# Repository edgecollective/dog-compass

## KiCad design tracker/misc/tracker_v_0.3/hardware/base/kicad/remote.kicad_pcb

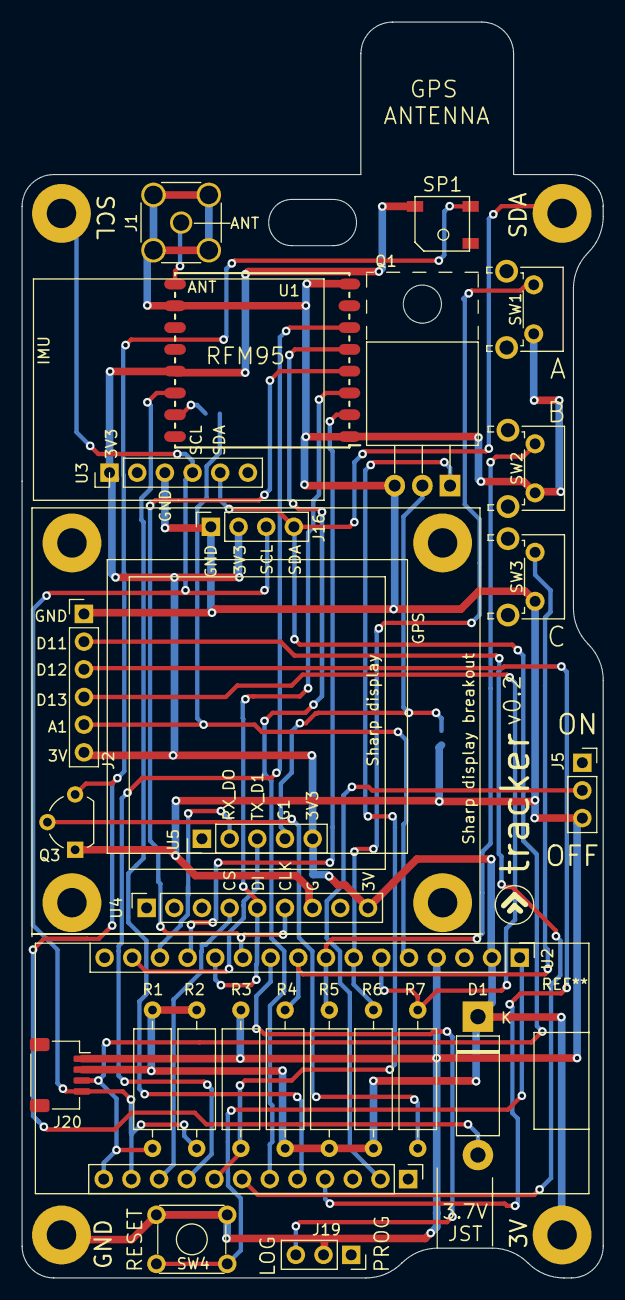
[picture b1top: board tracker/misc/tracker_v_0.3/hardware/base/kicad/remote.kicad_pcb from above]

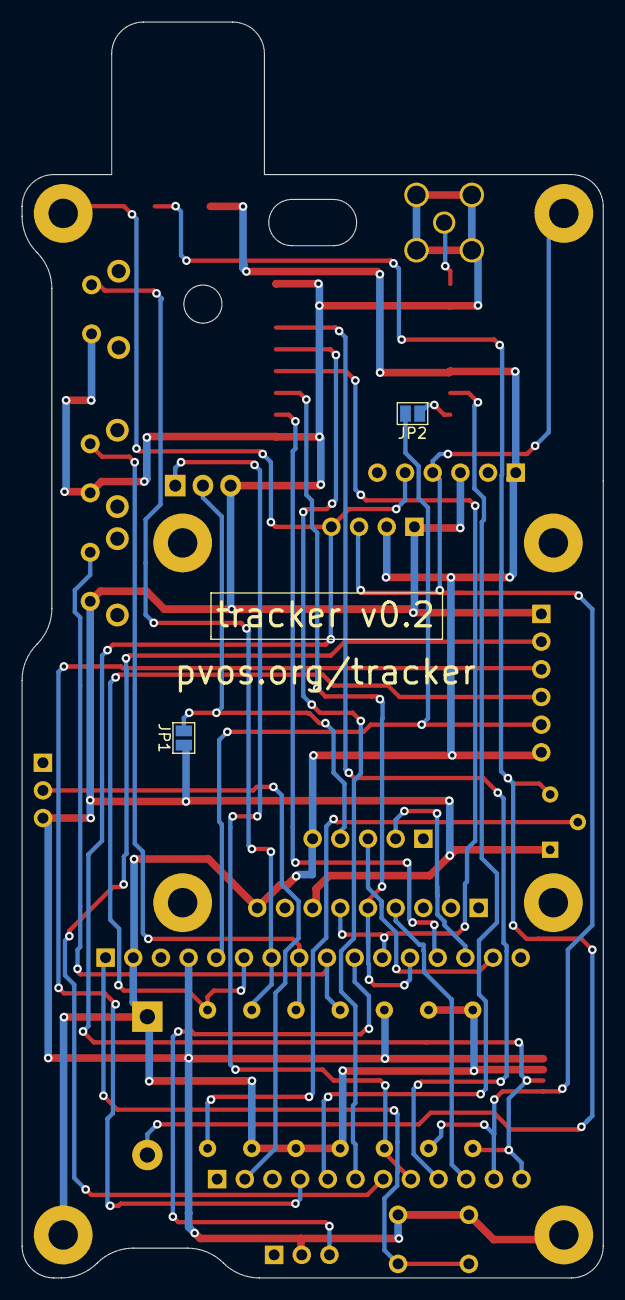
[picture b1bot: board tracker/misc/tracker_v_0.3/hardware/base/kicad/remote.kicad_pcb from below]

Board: 2 copper layers, 53.3 x 115.3 mm, 32 parts (2 on the bottom side), 29 nets.

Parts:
D1: DIODE; D_5W_P12.70mm_Horizontal
H1, H2, H5, H6: MountingHole_Pad; MountingHole_2.7mm_M2.5_Pad
J1: Conn_Coaxial; SMA_Amphenol_132134_Vertical
J2: Conn_01x06_Female; PinHeader_1x06_P2.54mm_Vertical
J5, J19: Conn_01x03_Female; PinSocket_1x03_P2.54mm_Vertical
J16: Conn_01x04_Female; PinSocket_1x04_P2.54mm_Vertical
J20: Conn_01x04_Female; JST_SH_SM04B-SRSS-TB_1x04-1MP_P1.00mm_Horizontal
JP1, JP2: Jumper_NO_Small; SolderJumper-2_P1.3mm_Open_Pad1.0x1.5mm
Q1: Q_NMOS_GDS; TO-220-3_Horizontal_TabUp
Q3: Q_NPN_EBC; TO-92L_Wide
R1, R2, R4, R5, R6: 4.7K; R_Axial_DIN0309_L9.0mm_D3.2mm_P12.70mm_Horizontal
R3: 10K; R_Axial_DIN0309_L9.0mm_D3.2mm_P12.70mm_Horizontal
R7: R; R_Axial_DIN0309_L9.0mm_D3.2mm_P12.70mm_Horizontal
SP1: SPEAKER_BUZZER5MM; BUZZER_SMT_5MM
SW1, SW2, SW3: SW_Push; SW_Tactile_SPST_Angled_PTS645Vx58-2LFS
SW4: SW_Push_Dual; SW_TH_Tactile_Omron_B3F-10xx
U1: RFM95HW; RFM95
U2: feather
U3: Adafruit_IMU_BNO005; IMU_Ada_BNO005
U4: Adafruit_Sharp_Display_1_3; Display_adafruit_sharp_13
U5: neo-6m-black; gps_neo6m_black

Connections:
+3V3: D1.1, H2.1, J2.6, J16.2, J20.2, R1.1, R2.1, R4.1, R5.1, R6.1, SP1.-, U1.13, U2.14, U3.1, U4.9, U5.5
A0: J2.5, JP2.2, U2.17
A1: J2.4, R7.2, U2.18
A2: R6.2, SW1.1, U2.19
A3: R5.2, SW2.1, U2.20
A4: R4.2, SW3.1, U2.21
A5: J19.3, U2.22
D5: U2.10, U4.4
D6: U1.6, U2.9
D9: Q1.1, R3.1, U2.8
D10: J2.2, U2.7
D11: U1.5, U2.6
D12: U1.14, U2.5
D13: J2.3, U2.4
EN: J5.2, U2.2
GND: H1.1, J1.2, J2.1, J5.3, J16.1, J19.2, J20.1, JP1.1, Q1.3, Q3.1, R3.2, SW1.2, SW2.2, SW3.2, SW4.3, SW4.4, U1.1, U1.8, U1.10, U2.16, U3.3, U4.7
MISO: U1.2, U2.25
MOSI: U1.3, U2.24, U4.5
unnamed: D1.2, Q3.3, SP1.+
unnamed: J1.1, U1.9
unnamed: JP2.1, U1.15
unnamed: Q3.2, R7.1
POWER_1: JP1.2, Q1.2, U5.4
RX_D0: U2.26, U5.2
SCK: U1.4, U2.23, U4.6
SCL: H6.1, J16.3, J20.4, R2.2, U2.11, U3.4
SDA: H5.1, J16.4, J20.3, R1.2, U2.12, U3.5
TX_D1: U2.27, U5.3
~RESET: SW4.1, SW4.2, U2.13

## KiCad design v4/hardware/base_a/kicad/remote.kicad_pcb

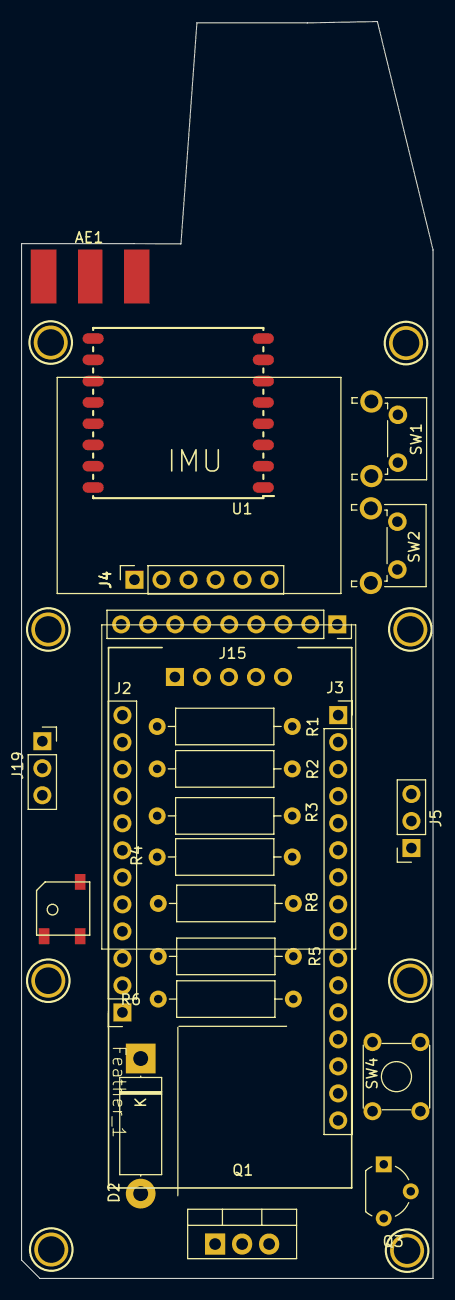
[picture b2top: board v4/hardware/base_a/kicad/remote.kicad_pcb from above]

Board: 2 copper layers, 38.7 x 118.2 mm, 31 parts (1 on the bottom side), 20 nets, no tracks yet.

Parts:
AE1: Antenna_Shield; RF_SMA_BoardEdge_142-0701-801
D2: DIODE; D_5W_P12.70mm_Horizontal
H3, H4, H7, H8, H9, H10, H11, H12: MountingHole; MOUNTINGHOLE_2.5_PLATED
J2: Conn_01x12_Female; PinSocket_1x12_P2.54mm_Vertical
J3: Conn_01x16_Female; PinSocket_1x16_P2.54mm_Vertical
J4: Conn_01x06_Female; PinSocket_1x06_P2.54mm_Vertical
J5, J19: Conn_01x03_Female; PinSocket_1x03_P2.54mm_Vertical
J6: Conn_01x05_Female; PinSocket_1x05_P2.54mm_Vertical
J15: Conn_01x09_Female; PinSocket_1x09_P2.54mm_Vertical
Q1: Q_NMOS_GDS; TO-220-3_Vertical
Q3: Q_NPN_EBC; TO-92L_Wide
R1, R2, R3, R4: 4.7K; R_Axial_DIN0309_L9.0mm_D3.2mm_P12.70mm_Horizontal
R5, R8: R; R_Axial_DIN0309_L9.0mm_D3.2mm_P12.70mm_Horizontal
R6: 10K; R_Axial_DIN0309_L9.0mm_D3.2mm_P12.70mm_Horizontal
SP1: SPEAKER_BUZZER5MM; BUZZER_SMT_5MM
SW1, SW2: SW_Push; SW_Tactile_SPST_Angled_PTS645Vx58-2LFS
SW4: SW_Push_Dual; SW_TH_Tactile_Omron_B3F-10xx
U1: RFM95HW; RFM95

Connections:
+3V3: D2.1 (K), J3.15, J4.1, J6.5, J15.1, R1.1, R2.1, R3.1, R4.1, SP1.-
A0: J3.12, R8.2
A3: J3.9, J19.3
A4: J3.8, R4.2, SW1.1
A5: J3.7, R3.2, SW2.1
D5: J2.10, J15.6
D9: J2.8, Q1.1 (G), R6.1
GND: J3.13, J4.3, J5.1, J15.3, Q1.3 (S), Q3.1 (E), R5.2, R6.2, SW1.2, SW2.2, SW4.3, SW4.4
MOSI: J3.5, J15.5
unnamed: D2.2 (A), Q3.3 (C), SP1.+
unnamed: J19.2, R5.1
unnamed: Q3.2 (B), R8.1
POWER_1: J6.4, Q1.2 (D)
RX_D0: J3.3, J6.2
SCK: J3.6, J15.4
SCL: J2.11, J4.4, R2.2
SDA: J2.12, J4.5, R1.2
TX_D1: J3.2, J6.3
VBAT: J2.1, J5.2
~RESET: J3.16, SW4.1, SW4.2

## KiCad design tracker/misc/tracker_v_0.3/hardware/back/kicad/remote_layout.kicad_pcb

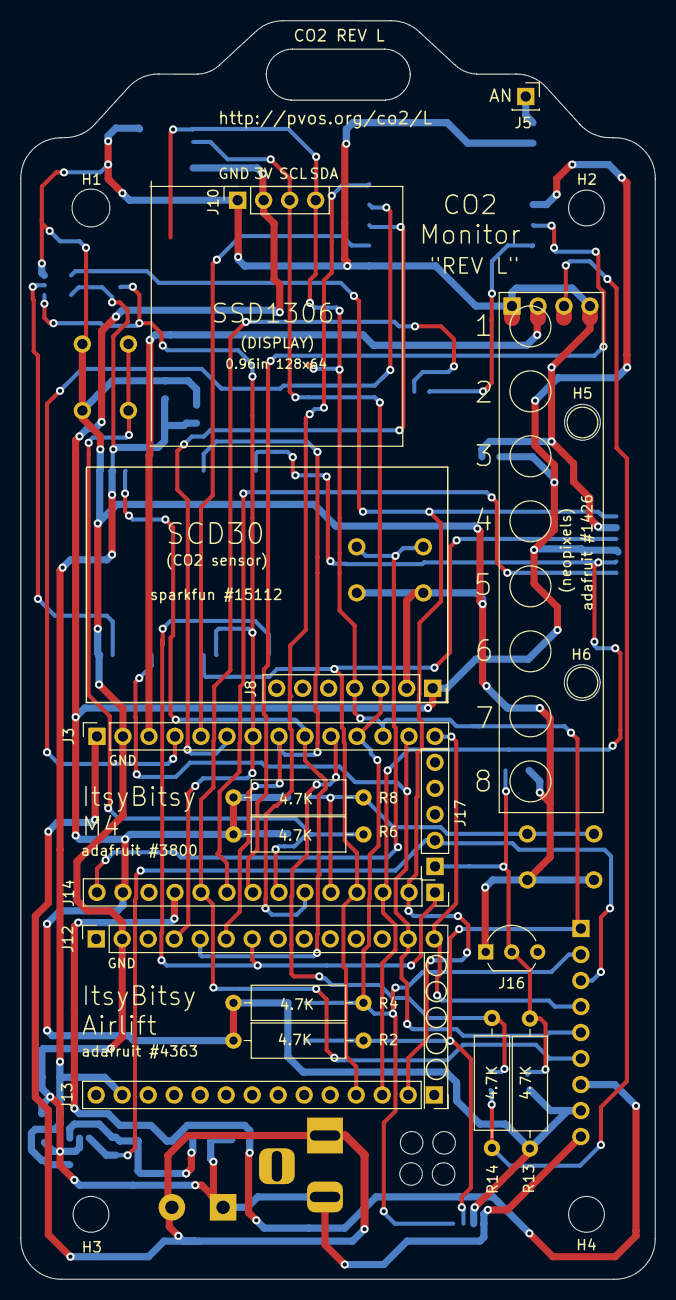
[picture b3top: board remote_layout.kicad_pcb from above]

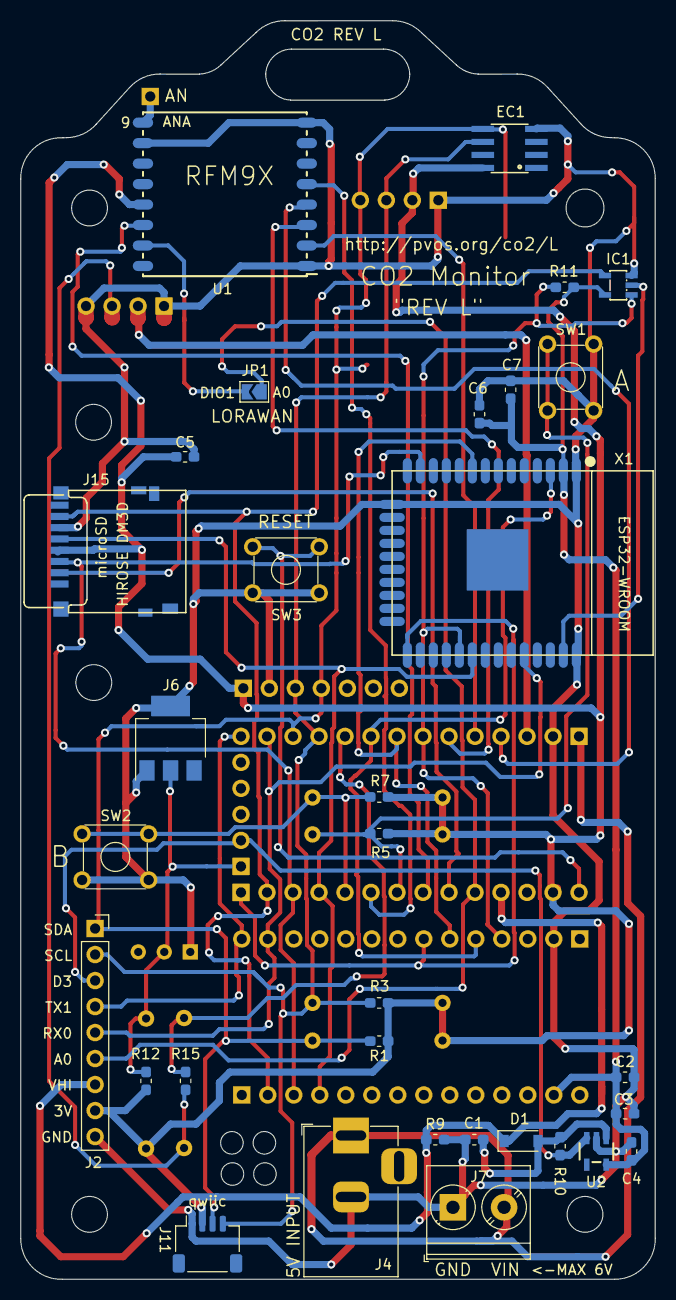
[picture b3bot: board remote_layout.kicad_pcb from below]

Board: 2 copper layers, 62.0 x 122.9 mm, 62 parts (32 on the bottom side), 35 nets.

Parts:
C1, C3, C4, C7: 10u; C_0603_1608Metric_Pad1.05x0.95mm_HandSolder
C2, C6: 0.1u; C_0603_1608Metric_Pad1.05x0.95mm_HandSolder
C5: 1u; C_0603_1608Metric_Pad1.05x0.95mm_HandSolder
D1: DIODE; D_SOD-123
EC1: ATECC108; SOIC8
H1: MountingHole; MountingHole_3.7mm
H2, H3, H4, H5, H6: MountingHole; MountingHole_3.5mm
H7, H8, H9, H10: MountingHole; MountingHole_2.2mm_M2
IC1: 74AHC1G125; SOT23-5L
J1: Conn_01x04_Female; PinSocket_1x04_P2.54mm_Vertical_no_silk
J2: Conn_01x09_Female; PinSocket_1x09_P2.54mm_Vertical
J3, J12, J13, J14: Conn_01x14_Female; PinSocket_1x14_P2.54mm_Vertical
J4: Barrel_Jack_MountingPin; BarrelJack_Horizontal
J5: Conn_01x01_Female; PinSocket_1x01_P2.54mm_Vertical
J6: Conn_01x04_Female; SOT-223
J7: Screw_Terminal_01x02; TerminalBlock_Phoenix_PT-1,5-2-5.0-H_1x02_P5.00mm_Horizontal
J8: SCD30; PinSocket_1x07_P2.54mm_Vertical
J10: ssd1306; PinSocket_1x04_P2.54mm_Vertical
J11: Conn_01x04_Female; JST_SH_SM04B-SRSS-TB_1x04-1MP_P1.00mm_Horizontal
J15: Micro_SD_Card; DM3D-SF_outline
J16: Conn_01x03_Female; TO-92_Inline_Wide
J17: Conn_01x05_Female; PinSocket_1x05_P2.54mm_Vertical
JP1: Jumper_NO_Small; SolderJumper-2_P1.3mm_Open_TrianglePad1.0x1.5mm
R1, R3: R; R_0603_1608Metric_Pad1.05x0.95mm_HandSolder
R2, R4: R; R_Axial_DIN0309_L9.0mm_D3.2mm_P12.70mm_Horizontal
R5, R7, R12: 4.7K; R_0603_1608Metric_Pad1.05x0.95mm_HandSolder
R6, R8, R13: 4.7K; R_Axial_DIN0309_L9.0mm_D3.2mm_P12.70mm_Horizontal
R9, R10: 100k; R_0603_1608Metric_Pad1.05x0.95mm_HandSolder
R11: 10K; R_0603_1608Metric_Pad1.05x0.95mm_HandSolder
R14: 500; R_Axial_DIN0309_L9.0mm_D3.2mm_P12.70mm_Horizontal
R15: 500; R_0603_1608Metric_Pad1.05x0.95mm_HandSolder
SW1, SW2, SW3: SW_Push_Dual; SW_TH_Tactile_Omron_B3F-10xx
TP1, TP2, TP3, TP4: TestPoint; TestPoint_Pad_1.0x1.0mm_no_silk
U1: RFM95HW; RFM95
U2: VREG_SOT23-5; SOT23-5
X1: ESP32_WROOM32; ESP32-WROOM

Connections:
2_ESP_GPIO0: J12.7, J14.1, X1.25
3VESP: C2.1, C3.1, C4.1, C6.1, C7.1, IC1.5, J13.13, R11.1, U2.5, X1.2
3_LDO_ENABLE: J2.3, J17.2, R10.2, U2.3
4_SERDAT: J6.2, J16.2, J17.1, R12.2, R13.2
5_NEOPIXEL: J3.10, R14.2, R15.2
7_ESP_RESET: J3.9, J12.5, X1.3
9_ESP_BUSY: J3.8, J12.6, X1.9
10_ESP_CS: IC1.1, J3.7, J12.4, R11.2, X1.29
11_LORA_MOSI: J3.6, U1.3
12_LORA_MISO: J3.5, U1.2
13_LORA_SCK: J3.4, U1.4
+3V3: C5.1, EC1.8, J2.8, J8.1, J10.2, J11.2, J14.13, J15.4, R1.1, R2.1, R3.1, R4.1, R5.1, R6.1, R7.1, R8.1, R12.1, R13.1, U1.13
A0_LORAWAN: J2.6, J14.10, JP1.1
A1_SD_CS: J14.9, J15.2
A2_LORA_IRQ: J14.8, U1.14
A3_BUTTON_A: J14.7, R5.2, R6.2, SW1.1, SW1.2
A4_LORA_CS: J14.6, U1.5
A5_BUTTON_B: J14.5, R7.2, R8.2, SW2.1, SW2.2
ESP_MISO: IC1.2, X1.37
ESP_RX: J2.5, J3.13, J12.13, X1.34
EXP_TX: J2.4, J3.14, J12.14
GND: C1.2, C2.2, C3.2, C4.2, C5.2, C6.2, C7.2, EC1.4, IC1.3, J1.1, J1.4, J2.9, J3.2, J4.2, J6.1, J6.4, J7.1, J8.2, J10.1, J11.1, J12.2, J15.6, J16.1, R9.2, SW1.3, SW1.4, SW2.3, SW2.4, SW3.3, SW3.4, TP1.1, TP4.1, U1.1, U1.8, U1.10, U2.2, X1.1, X1.15, X1.38
LORA_DIO1: JP1.2, U1.15
MISO: IC1.4, J13.2, J14.2, J15.7
MOSI: J13.3, J14.3, J15.3, X1.13
unnamed: C1.1, D1.2, R10.1, U2.1
unnamed: J1.3, R14.1, R15.1, TP3.1
unnamed: J5.1, U1.9
SCK: J13.4, J14.4, J15.5, X1.30
SCL: EC1.6, J2.2, J3.11, J8.3, J10.3, J11.4, R3.2, R4.2
SDA: EC1.5, J2.1, J3.12, J8.4, J10.4, J11.3, R1.2, R2.2
VBAT: J3.1, J4.1, J7.2
VBUS: J1.2, J3.3, TP2.1
VHI: D1.1, J2.7, J14.11, R9.1
~RESET: J14.14, SW3.1, SW3.2

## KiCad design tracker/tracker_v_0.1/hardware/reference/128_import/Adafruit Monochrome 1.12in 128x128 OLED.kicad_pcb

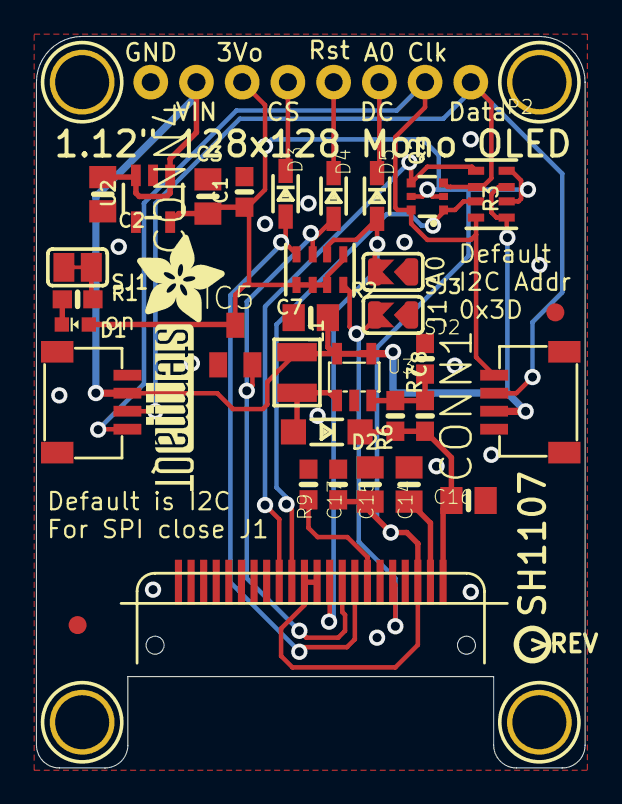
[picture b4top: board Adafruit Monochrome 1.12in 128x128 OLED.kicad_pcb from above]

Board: 2 copper layers, 30.5 x 40.6 mm, 41 parts (0 on the bottom side), 21 nets.

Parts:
C1, C8: 0.1uF; 0603-NO
C2, C3, C7, C14, C15, C16: 10uF; 0805-NO
C17: 1uF; 0603-NO
CONN1, CONN4: STEMMA_I2C_QT; JST_SH4
D1: GREEN; CHIPLED_0603_NOOUTLINE
D2: MBR120; SOD-123
D3, D4, D5: 1N4148; SOD-323
FID3, FID4: FIDUCIAL_1MM
IC5: APX803; SOT23
JP2: HEADER-1X876MIL; 1X08_ROUND_76
L1: 10uH; INDUCTOR_1007
Q2: BSS138; SOT363
R1, R7: 10K; 0603-NO
R2, R3: 10K; RESPACK_4X0603
R6: 100K; 0603-NO
R9: 390K; 0603-NO
SJ1: SOLDERJUMPERCLOSED; SOLDERJUMPER_CLOSEDWIRE
SJ2, SJ3: SOLDERJUMPER; SOLDERJUMPER_ARROW_NOPASTE
U2: AP2112K-3.3; SOT23-5
U3: FAN5331SX; SOT23-5@1
U$1, U$17, U$19, U$21: MOUNTINGHOLE3.0THIN; MOUNTINGHOLE_3.0_PLATEDTHIN
U$8: ADAFRUIT_5MM
U$25: PCBFEAT-REV-040
U$31: STEMMAQT
X2: OLED_1.12_128X128_MONO; OLED_1.12IN_128X128MONO

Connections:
3.3V: C1.1, C3.1, C15.2, C17.2, D1.A, IC5.3, JP2.6, Q2.2, Q2.5, R2.1, R2.5, R2.6, R2.7, R3.2, R3.4, U2.5, X2.3, X2.11, X2.12
12V: C8.1, C16.2, D2.C, R6.2, X2.1
/CS_3.3V: D3.A, R2.4, X2.8
/CS_5.0V: D3.C, JP2.5
/D0/SCLK/SCK_3.3V: Q2.1, R3.7, X2.13
/D1/MOSI/SDA1_3.3V: Q2.4, R3.5, X2.14
/DC/SA0_3.3V: D5.A, R2.2, SJ3.2, X2.10
/DC/SA0_5.0V: D5.C, JP2.3
/RST_3.3V: D4.A, IC5.2, R2.3, X2.9
/RST_5.0V: D4.C, JP2.4
/SCL: CONN1.4, CONN4.4, JP2.2, Q2.6, R3.8
/SDA: CONN1.3, CONN4.3, JP2.1, Q2.3, R3.6
GND: C1.2, C2.2, C3.2, C7.2, C14.1, C15.1, C16.1, C17.1, CONN1.1, CONN4.1, IC5.1, JP2.8, R7.1, R9.1, SJ1.2, SJ2.1, SJ3.1, U2.2, U3.2, X2.4, X2.6, X2.15, X2.16, X2.17, X2.18, X2.19, X2.20, X2.21, X2.22
unnamed: C8.2, R6.1, R7.2, U3.3
unnamed: C14.2, X2.2
unnamed: D1.C, R1.1
unnamed: D2.A, L1.P$2, U3.1
unnamed: R1.2, SJ1.1
unnamed: R2.8, SJ2.2, X2.5
unnamed: R9.2, X2.7
VCC: C2.1, C7.1, CONN1.2, CONN4.2, JP2.7, L1.P$1, R3.1, R3.3, U2.1, U2.3, U3.4, U3.5

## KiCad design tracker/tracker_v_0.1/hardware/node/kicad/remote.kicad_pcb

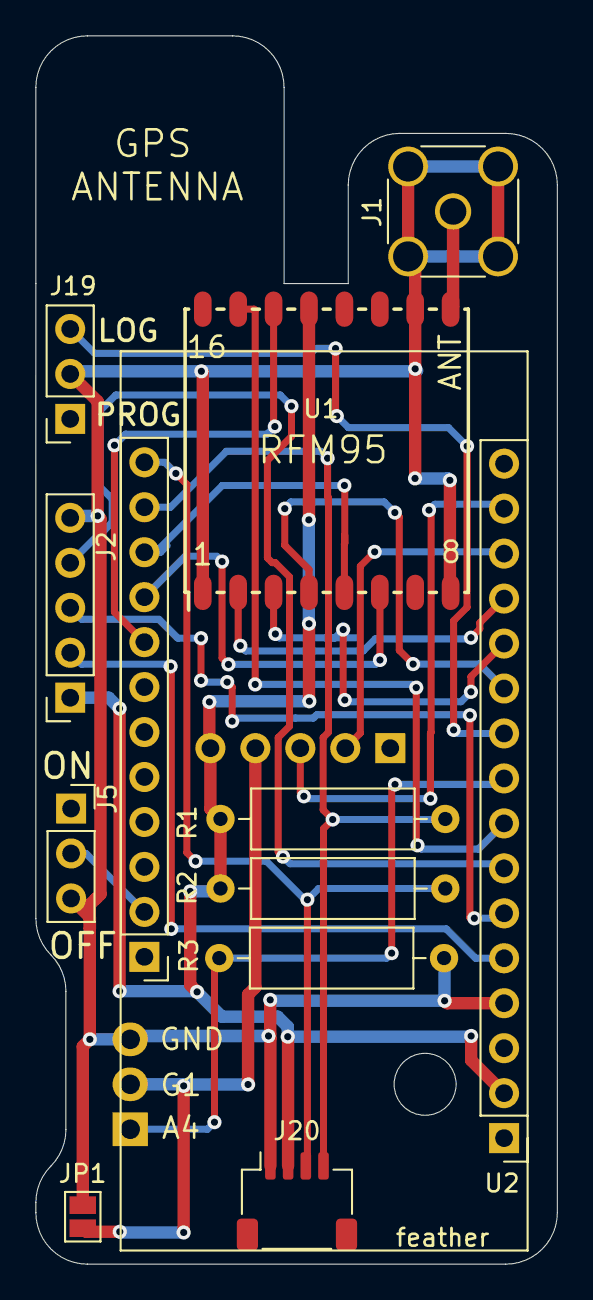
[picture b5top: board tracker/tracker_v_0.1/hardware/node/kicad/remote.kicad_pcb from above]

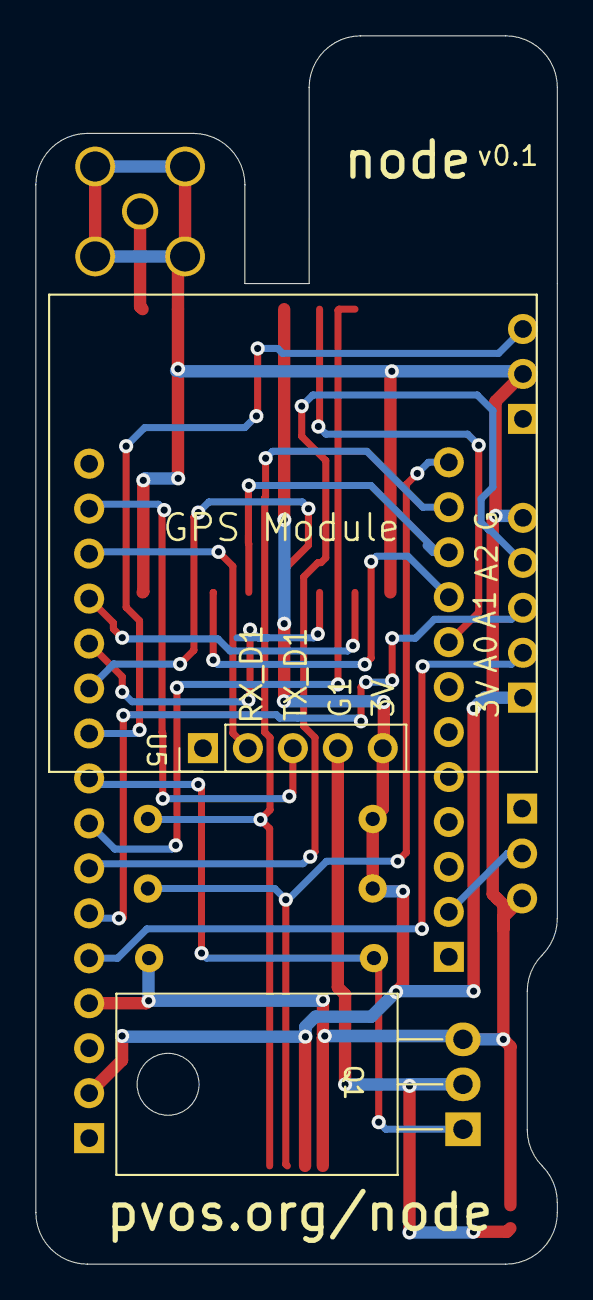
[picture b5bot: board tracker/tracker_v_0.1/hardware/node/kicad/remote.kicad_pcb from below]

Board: 2 copper layers, 29.5 x 69.4 mm, 13 parts (2 on the bottom side), 21 nets.

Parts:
J1: Conn_Coaxial; SMA_Amphenol_132134_Vertical
J2: Conn_01x05_Female; PinSocket_1x05_P2.54mm_Vertical
J5, J19: Conn_01x03_Female; PinSocket_1x03_P2.54mm_Vertical
J20: Conn_01x04_Female; JST_SH_SM04B-SRSS-TB_1x04-1MP_P1.00mm_Horizontal
JP1: Jumper_NO_Small; SolderJumper-2_P1.3mm_Open_Pad1.0x1.5mm
Q1: Q_NMOS_GDS; TO-220-3_Horizontal_TabDown
R1, R2: 4.7K; R_Axial_DIN0309_L9.0mm_D3.2mm_P12.70mm_Horizontal
R3: 10K; R_Axial_DIN0309_L9.0mm_D3.2mm_P12.70mm_Horizontal
U1: RFM95HW; RFM95
U2: feather
U5: neo-6m-black; gps_neo6m_black

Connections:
+3V3: J2.1, J20.2, R1.1, R2.1, U1.13, U2.14, U5.5
A0: J2.2, U2.17
A1: J2.3, U2.18
A2: J2.4, U2.19
A3: U1.15, U2.20
A4: Q1.1, R3.1, U2.21
A5: J19.3, U2.22
D5: U1.5, U2.10
D6: U1.6, U2.9
D9: U1.14, U2.8
EN: J5.2, U2.2
GND: J1.2, J2.5, J5.3, J19.2, J20.1, JP1.1, Q1.3, R3.2, U1.1, U1.8, U1.10, U2.16
MISO: U1.2, U2.25
MOSI: U1.3, U2.24
unnamed: J1.1, U1.9
POWER_1: JP1.2, Q1.2, U5.4
RX_D0: U2.26, U5.2
SCK: U1.4, U2.23
SCL: J20.4, R1.2, U2.11
SDA: J20.3, R2.2, U2.12
TX_D1: U2.27, U5.3

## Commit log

2021-10-29 fixed display
2021-12-24 working version
2021-12-29 decent layout
2021-12-30 basic layout
2022-01-05 nice board layout for v4 base_b
2022-01-05 routed power lines
2022-01-05 fully routed power lines
2022-01-07 reorg
2022-01-08 node repackaging
2022-01-09 fully routed node
2022-01-09 added gerbers
2022-01-12 fixed flipped sharp display header
2022-01-13 gridsquare working
2022-01-14 radgrid tests radio and spi display working together
2022-01-14 got compass more or less working
2022-01-22 updated trace to include a trace
2022-01-22 added live lat and lon
2022-01-23 wipe trace when change locators
2022-01-23 compass functionality
2022-01-27 gps_radio has basic functionality
2022-01-27 update to gps_radio
2022-01-27 base_gaps_radio.py is a good version
2022-01-28 working pair of remote and base
2022-01-29 upadet
2022-01-30 working pair of node_v_0.1 and tracker_v_o.2 firmware
2022-01-31 simulate person and dog walking and compute bearing and distance to dog using regulat python floats (double prec.) and single precision using numpy types
2022-02-03 update w/ raw lib
